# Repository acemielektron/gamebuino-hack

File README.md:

# gamebuino-hack
A diy clone of open source [gamebuino classic](http://legacy.gamebuino.com/wiki)

**Differences in hardware**
  - Hack is based on Atmega328 PDIP so it does not have A6 and A7 (PC6 and PC7) pins
  - Button C is moved to D5 (PD5) -> rebuilding all games and bootloader needed for this change to work
  - Battery sensor is moved to ADC3 (PC3) -> rebuilding all games are needed for this change to work
  - No ambient light sensor
  - No pwm control for background led

**Bootloader**
  - gamebuino requires a [custom bootloader](https://github.com/ghalfacree/Arduino-Sketches/tree/master/hardware/arduino/bootloaders/gamebuino_boot) for loading games from sd-card to work
  - gamebuino bootloader only supports fat16 formatted sd cards

**Pictures**

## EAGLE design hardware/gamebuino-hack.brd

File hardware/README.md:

# gamebuino-hack (eagle cad files)
A diy clone of open source [gamebuino classic](http://legacy.gamebuino.com/wiki)

**Differences in hardware**
  - Hack is based on Atmega328 PDIP so it does not have A6 and A7 (PC6 and PC7) pins
  - Button C is moved to D5 (PD5) -> rebuilding all games and bootloader needed for this change to work
  - Battery sensor is moved to ADC3 (PC3) -> rebuilding all games are needed for this change to work
  - No ambient light sensor
  - No pwm control for background led

**Bootloader**
  - gamebuino requires a [custom bootloader](https://github.com/ghalfacree/Arduino-Sketches/tree/master/hardware/arduino/bootloaders/gamebuino_boot) for loading games from sd-card to work
  - gamebuino bootloader only supports fat16 formatted sd cards

**Schematic**

**PCB**

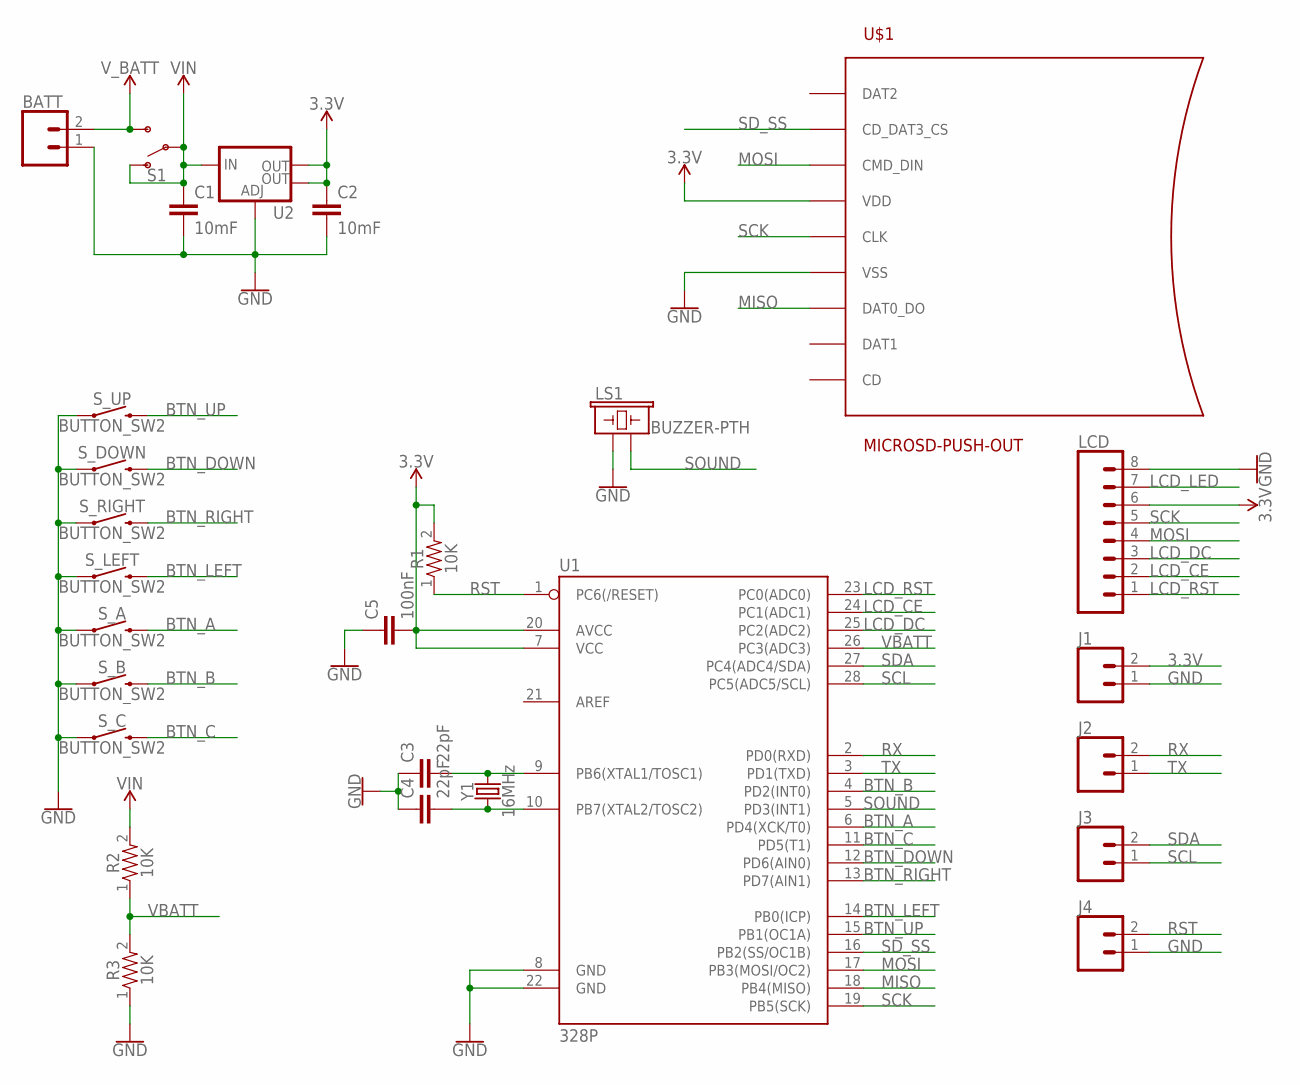
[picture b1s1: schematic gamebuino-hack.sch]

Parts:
BATT: CONN_02; 1X02
C1, C2: 10mF; 0805
C3, C4: 22pF; 0805
C5: 100nF; 0805
J1, J2, J3, J4: CONN_02; 1X02
LCD: CONN_08"; 1X08
LS1: BUZZER-PTH; BUZZER-12MM
R1, R2, R3: 10K; 0805
S1: SWITCH-SPDT-PTH-11.6X4.0MM; SWITCH_SPDT_PTH_11.6X4.0MM
S_A: BUTTON_SW2
S_B: BUTTON_SW2
S_C: BUTTON_SW2
S_DOWN: BUTTON_SW2
S_LEFT: BUTTON_SW2
S_RIGHT: BUTTON_SW2
S_UP: BUTTON_SW2
U1: 328P; DIP28
U2: V_REG_LM1117SOT223; SOT223
U$1: MICROSD-PUSH-OUT
Y1: 16MHz; HC49US

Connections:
3.3V: C2.1, C5.2, J1.2, LCD.6, R1.2, U1.7 (VCC), U1.20 (AVCC), U2.2 (OUT), U2.4 (OUT), U$1.4 (VDD)
BTN_A: S_A.2, U1.6 (PD4(XCK/T0))
BTN_B: S_B.2, U1.4 (PD2(INT0))
BTN_C: S_C.2, U1.11 (PD5(T1))
BTN_DOWN: S_DOWN.2, U1.12 (PD6(AIN0))
BTN_LEFT: S_LEFT.2, U1.14 (PB0(ICP))
BTN_RIGHT: S_RIGHT.2, U1.13 (PD7(AIN1))
BTN_UP: S_UP.2, U1.15 (PB1(OC1A))
GND: BATT.1, C1.2, C2.2, C3.1, C4.1, C5.1, J1.1, J4.1, LCD.8, LS1.+ (1), R3.1, S_A.1, S_B.1, S_C.1, S_DOWN.1, S_LEFT.1, S_RIGHT.1, S_UP.1, U1.8 (GND), U1.22 (GND), U2.1 (ADJ), U$1.6 (VSS), U$1.G1 (VSS), U$1.G2 (VSS), U$1.G3 (VSS), U$1.G4 (VSS)
LCD_CE: LCD.2, U1.24 (PC1(ADC1))
LCD_DC: LCD.3, U1.25 (PC2(ADC2))
LCD_LED: LCD.7
LCD_RST: LCD.1, U1.23 (PC0(ADC0))
MISO: U1.18 (PB4(MISO)), U$1.7 (DAT0_DO)
MOSI: LCD.4, U1.17 (PB3(MOSI/OC2)), U$1.3 (CMD_DIN)
unnamed: C3.2, U1.9 (PB6(XTAL1/TOSC1)), Y1.2
unnamed: C4.2, U1.10 (PB7(XTAL2/TOSC2)), Y1.1
RST: J4.2, R1.1, U1.1 (PC6(/RESET))
RX: J2.2, U1.2 (PD0(RXD))
SCK: LCD.5, U1.19 (PB5(SCK)), U$1.5 (CLK)
SCL: J3.1, U1.28 (PC5(ADC5/SCL))
SDA: J3.2, U1.27 (PC4(ADC4/SDA))
SD_SS: U1.16 (PB2(SS/OC1B)), U$1.2 (CD_DAT3_CS)
SOUND: LS1.- (2), U1.5 (PD3(INT1))
TX: J2.1, U1.3 (PD1(TXD))
VBATT: R2.1, R3.2, U1.26 (PC3(ADC3))
VIN: C1.1, R2.2, S1.1 (O), S1.2, U2.3 (IN)
V_BATT: BATT.2, S1.3 (S)

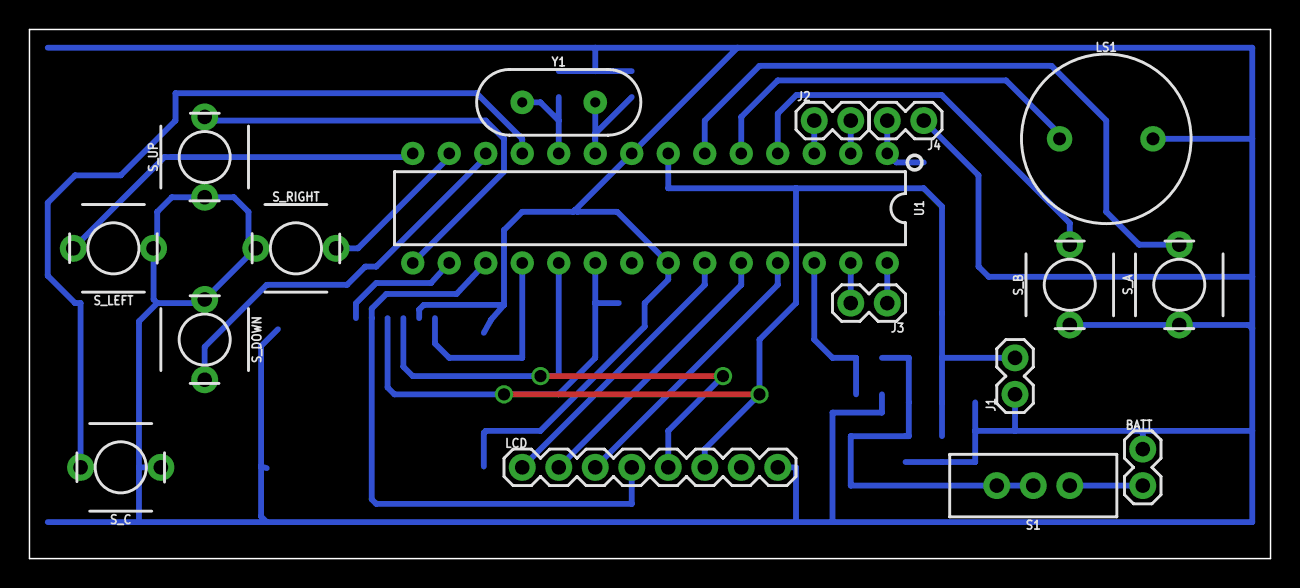
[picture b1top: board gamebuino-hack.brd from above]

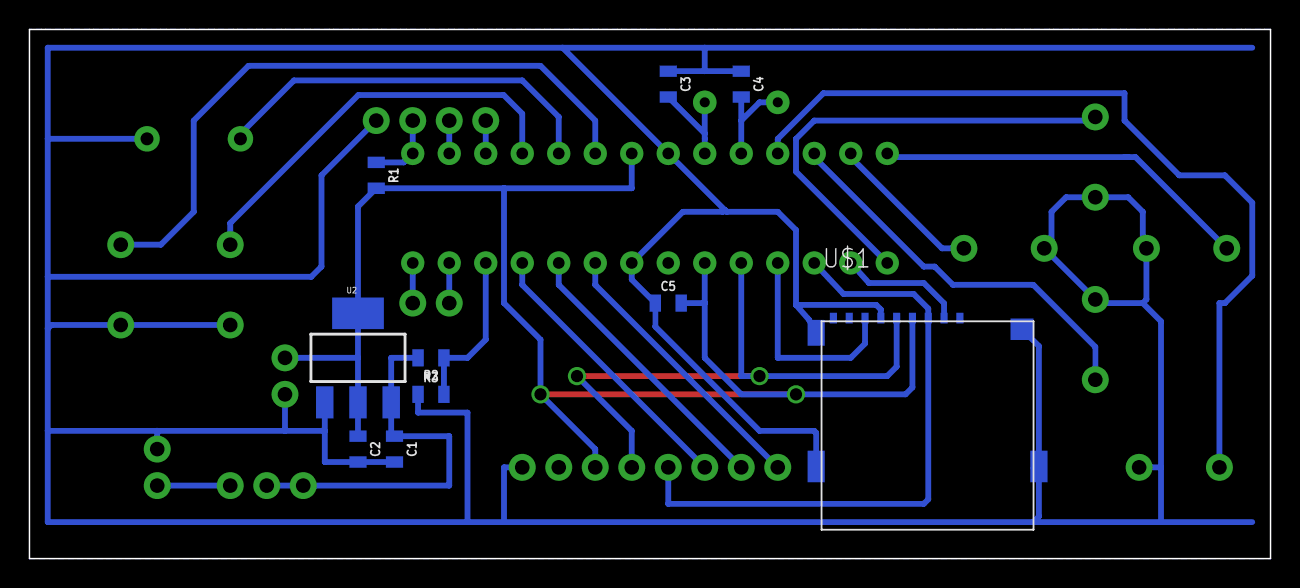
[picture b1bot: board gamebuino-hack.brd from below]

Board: 2 copper layers, 86.4 x 36.8 mm, 27 parts (10 on the bottom side), 27 nets.

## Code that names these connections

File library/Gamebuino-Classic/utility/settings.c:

/*
 * (C) Copyright 2014 Aurélien Rodot. All rights reserved.
 *
 * This file is part of the Gamebuino Library (http://gamebuino.com)
 *
 * The Gamebuino Library is free software: you can redistribute it and/or modify
 * it under the terms of the GNU Lesser General Public License as published by
 * the Free Software Foundation, either version 3 of the License, or
 * (at your option) any later version.
 *
 * This program is distributed in the hope that it will be useful,
 * but WITHOUT ANY WARRANTY; without even the implied warranty of
 * MERCHANTABILITY or FITNESS FOR A PARTICULAR PURPOSE.  See the
 * GNU Lesser General Public License for more details.
 *
 * You should have received a copy of the GNU Lesser General Public License
 * along with this program.  If not, see <http://www.gnu.org/licenses/>
 */

#ifndef SETTINGS_C
#define	SETTINGS_C

#define NOROT 0
#define ROTCCW 1
#define ROT180 2
#define ROTCW 3

//SETTINGS YOU CAN EDIT

#define NUM_CHANNELS 4 //number of sound channels, between 0 and 4
#define DISPLAY_ROT NOROT //set to NOROT, ROTCCW, ROT180 or ROTCW. Can be used to play in portrait mode.
#define ENABLE_GUI 1 //enable menu, keyboard, pop-up, volume adjust functions
#define ENABLE_BITMAPS 1 //will replace bitmaps with rectangles if disabled
#define ENABLE_GRAYSCALE 1 //allows the use of the GRAY color
#define EXTENDED_NOTE_RANGE 1 //allows the use of notes above A 5... please avoid that they sound really bad

//not really useful
#define ENABLE_BATTERY 1 //disable battery monitoring
#define ENABLE_BACKLIGHT 0 //disable automatic back-light

//IT'S STRONGLY ADVISED TO LEAVE THE FOLLOWING SETTINGS ALONE

//defaults values of settings which can be adjusted on each Gamebuino using settings.hex
#define SCR_CONTRAST 60
#define START_MENU_TIMER 255 //40 = 40 frames (2sec) before start menu is skipped, 0 = no start menu, 255 = start menu until you press A

//addresses of settings stored in the program memory
#define SETTINGS_PAGE ((const char *)(0x7800-128))
#define SETTINGS_TOKEN 			0xC001
#define OFFSET_CURRENTGAME		2
#define OFFSET_USERNAME			11
#define USERNAME_LENGTH			10
#define OFFSET_CONTRAST			22
#define OFFSET_BACKLIGHT_MIN	23
#define OFFSET_BACKLIGHT_MAX	24
#define OFFSET_LIGHT_MIN		25
#define OFFSET_LIGHT_MAX		27
#define OFFSET_VOLUME_MAX		29
#define OFFSET_VOLUME_DEFAULT	30
#define OFFSET_START_MENU_TIMER	31
#define OFFSET_BATTERY_CRITIC	32
#define OFFSET_BATTERY_LOW		34
#define OFFSET_BATTERY_MED		36
#define OFFSET_BATTERY_FULL		38

//GUI
#define KEYBOARD_W 16
#define KEYBOARD_H 8

//screen
#define SCR_CLK 13
#define SCR_DIN 11
#define SCR_DC  A2
#define SCR_CS  A1
#define SCR_RST A0

//sound
#define VOLUME_GLOBAL_MAX 7
#define VOLUME_CHANNEL_MAX 255/NUM_CHANNELS/7/9 //7=instrument volume 9=note volume

//battery voltage monitor
#define BAT_PIN A3
#define NUM_LVL 4
#define BAT_LVL_CRITIC  3500
#define BAT_LVL_LOW		3550
#define BAT_LVL_MED		3700
#define BAT_LVL_FULL	3900

//SD card
#define SD_CS 10

//screens back light
#define BACKLIGHT_PIN -1
//auto back-light levels
#define BACKLIGHT_MIN 0
#define BACKLIGHT_MAX 255

//ambient light sensor
#define AMBIENTLIGHT_PIN -1
//auto back-light levels
#define AMBIENTLIGHT_MIN 800 //800
#define AMBIENTLIGHT_MAX 980 //1000
#define AMBIENTLIGHT_SMOOTHING 16

//number of buttons
#define NUM_BTN         7
//buttons ID
#if DISPLAY_ROT == 0
	#define BTN_UP      1
	#define BTN_RIGHT   2
	#define BTN_DOWN    3
	#define BTN_LEFT    0
#elif DISPLAY_ROT == ROTCCW
	#define BTN_UP      2
	#define BTN_RIGHT   3
	#define BTN_DOWN    0
	#define BTN_LEFT    1
#elif DISPLAY_ROT == ROT180
	#define BTN_UP      3
	#define BTN_RIGHT   0
	#define BTN_DOWN    1
	#define BTN_LEFT    2
#elif DISPLAY_ROT == ROTCW
	#define BTN_UP      0
	#define BTN_RIGHT   1
	#define BTN_DOWN    2
	#define BTN_LEFT    3
#endif
#define BTN_A           4
#define BTN_B           5
#define BTN_C           6
//buttons pins
#define BTN_UP_PIN      9
#define BTN_RIGHT_PIN   7
#define BTN_DOWN_PIN    6
#define BTN_LEFT_PIN    8
#define BTN_A_PIN       4
#define BTN_B_PIN       2
#define BTN_C_PIN       5

#endif /* SETTINGS_C */

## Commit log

2019-12-23 eagle files
2019-12-24 Add files via upload
    Unmodified boot loader source
2019-12-24 Modify bootloader for button C at D5
2019-12-24 Cleanup
2019-12-24 Compiled but untested bootloader
2019-12-24 Corrected sound output (removed cap)
2019-12-27 Added delay before reading button C Reading button C immediately after setting internal pullup was causing bootlock adding a delay cost additional 12 bytes in bootloader but prevented bootlock.
2019-12-27 Add build images Added images of hack build
2019-12-27 Add images
2019-12-27 Correct images
2019-12-30 Recompile games
2019-12-30 patch b-rally to work with hack
2019-12-30 Add gamebuino-classic arduino library for reference
2019-12-30 Modified utility/settings.c to work with hack
2019-12-30 Add gamebuino-classic arduino library

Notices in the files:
parts and their libraries:
SparkFun-Connectors: Licensing: Creative Commons ShareAlike 4.0 International - https://creativecommons.org/licenses/by-sa/4.0
